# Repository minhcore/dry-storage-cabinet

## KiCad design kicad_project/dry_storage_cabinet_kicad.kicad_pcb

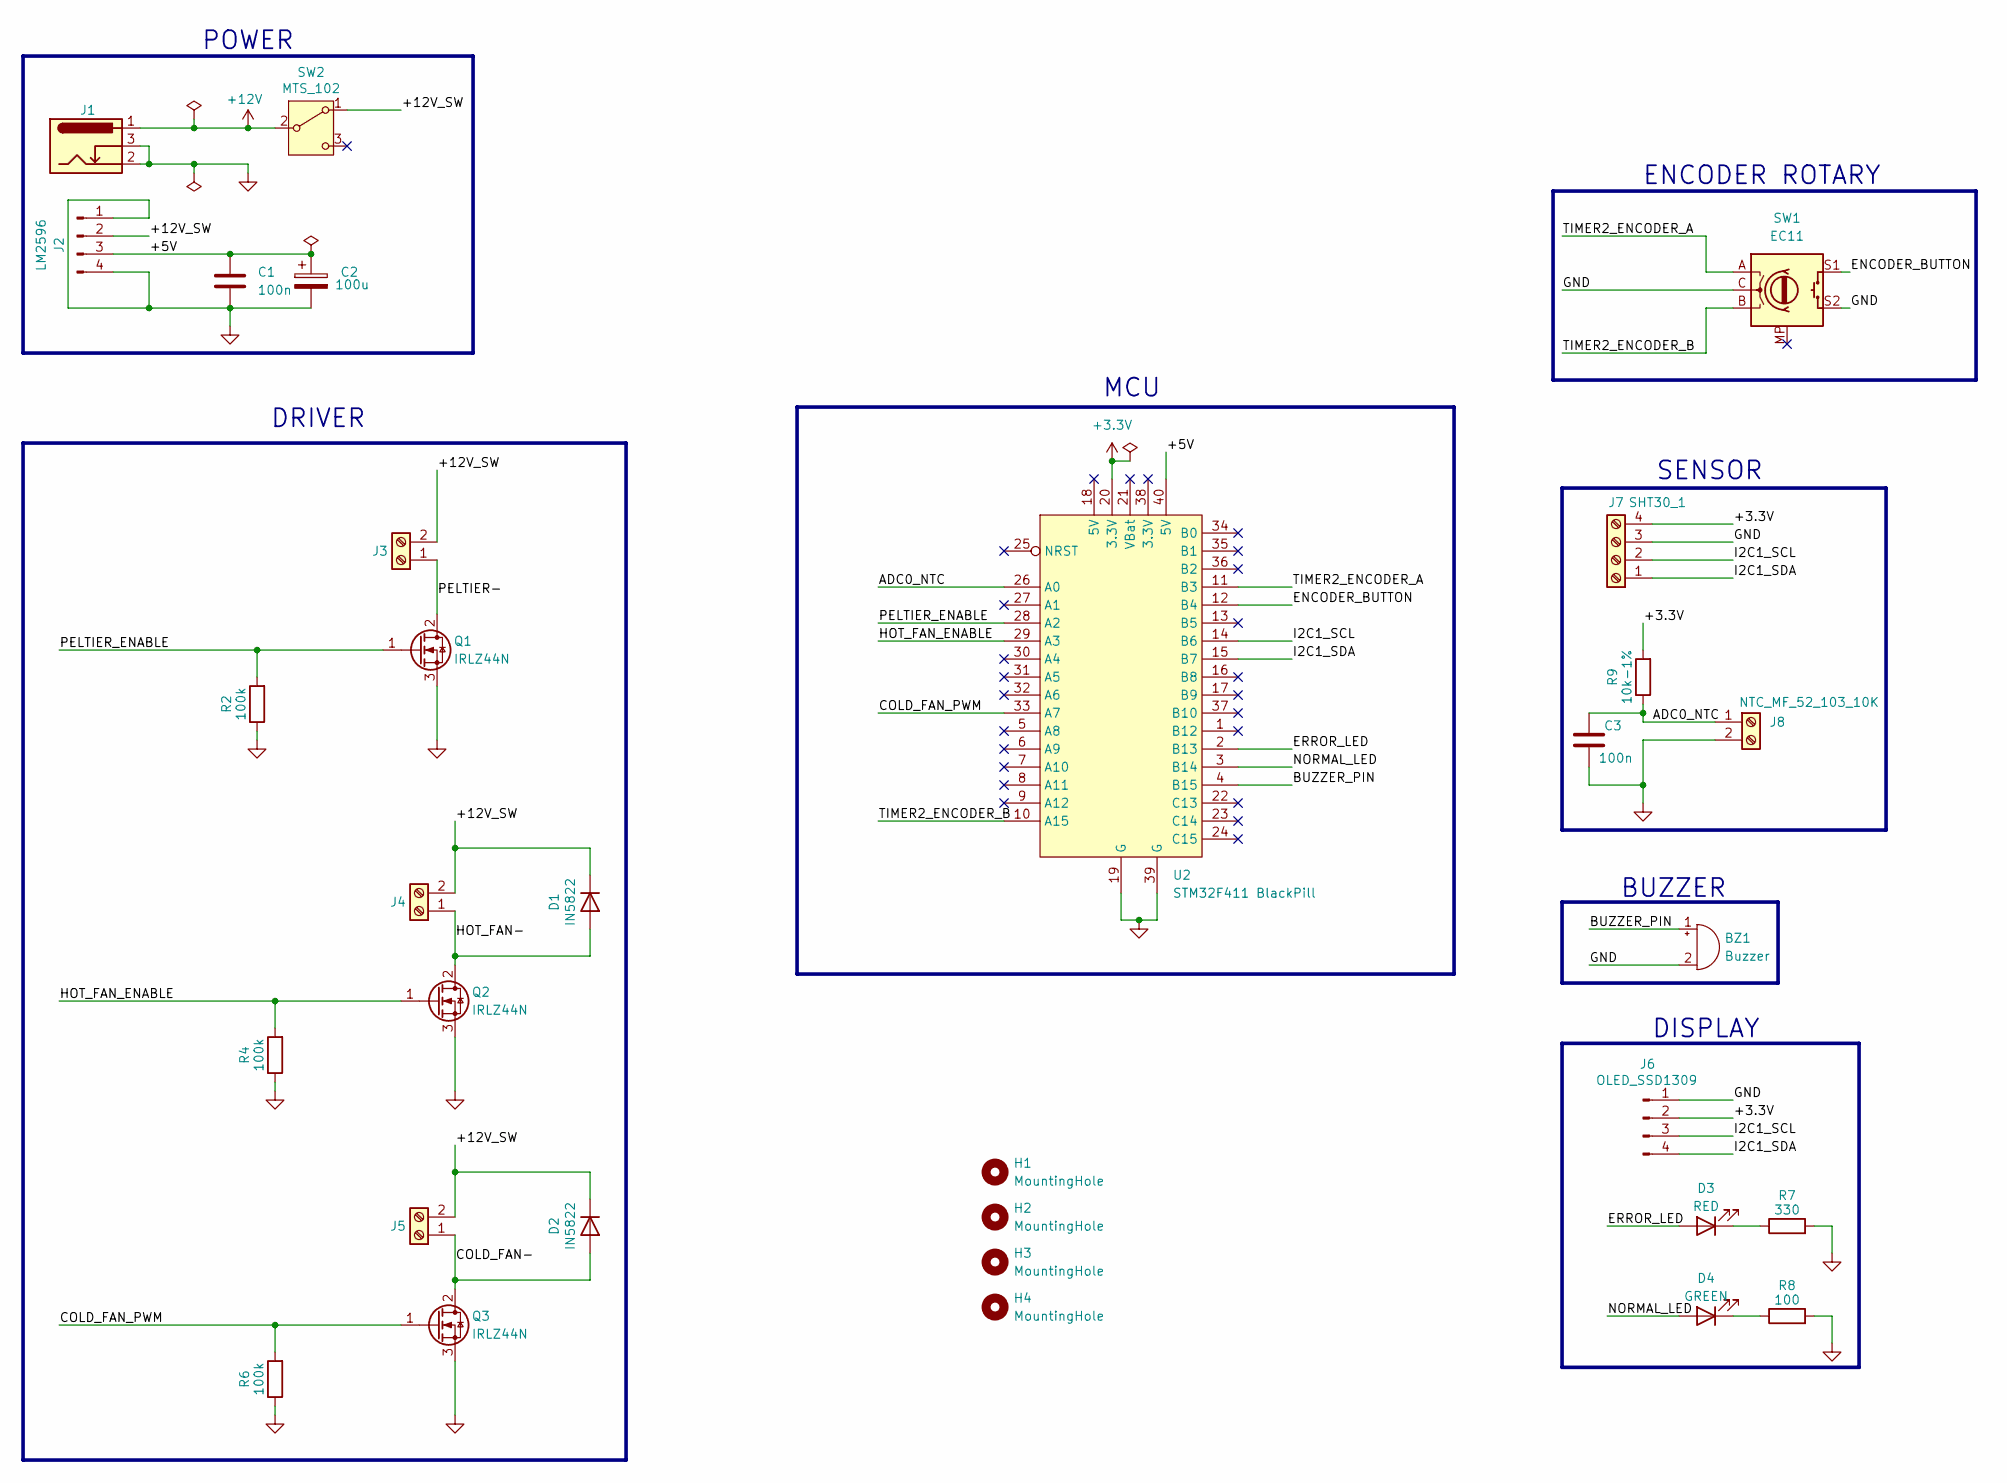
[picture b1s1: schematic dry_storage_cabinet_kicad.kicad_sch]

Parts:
BZ1: Buzzer; Buzzer_12x9.5RM7.6
C1, C3: 100n; C_Disc_D5.0mm_W2.5mm_P5.00mm
C2: 100u; CP_Radial_D6.3mm_P2.50mm
D1, D2: IN5822; D_DO-201AD_P15.24mm_Horizontal
D3: RED; LED_D3.0mm
D4: GREEN; LED_D3.0mm
H1, H2, H3, H4: MountingHole; MountingHole_3.2mm_M3
J1: Barrel_Jack_Switch; BarrelJack_GCT_DCJ200-10-A_Horizontal
J2: LM2596; LM2596-DC-DC
J3, J4, J5: Screw_Terminal_01x02; TerminalBlock_MaiXu_MX126-5.0-02P_1x02_P5.00mm
J6: OLED_SSD1309; PinHeader_1x04_P2.54mm_Vertical
J7: SHT30_1; TerminalBlock_MaiXu_MX126-5.0-04P_1x04_P5.00mm
J8: NTC_MF_52_103_10K; TerminalBlock_MaiXu_MX126-5.0-02P_1x02_P5.00mm
Q1, Q2, Q3: IRLZ44N; TO-220-3_Vertical
R2, R4, R6: 100k; R_Axial_DIN0207_L6.3mm_D2.5mm_P10.16mm_Horizontal
R7: 330; R_Axial_DIN0207_L6.3mm_D2.5mm_P10.16mm_Horizontal
R8: 100; R_Axial_DIN0207_L6.3mm_D2.5mm_P10.16mm_Horizontal
R9: 10k-1%; R_Axial_DIN0207_L6.3mm_D2.5mm_P10.16mm_Horizontal
SW1: EC11; RotaryEncoder_Alps_EC11E-Switch_Vertical_H20mm_MountingHoles
SW2: MTS_102; MTS102
U2: STM32F411 BlackPill; STM32F411_Black_Pill

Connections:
+3.3V: J6.2, J7.4, R9.2, U2.20 (3.3V)
+12V: J1.1, SW2.2 (B)
/+5V: C1.1, C2.1, J2.3, U2.40 (5V)
/+12V_SW: D1.1 (K), D2.1 (K), J2.2, J3.2, J4.2, J5.2, SW2.1 (A)
/ADC0_NTC: C3.1, J8.1, R9.1, U2.26 (A0)
/BUZZER_PIN: BZ1.1 (+), U2.4 (B15)
/COLD_FAN-: D2.2 (A), J5.1, Q3.2 (D)
/COLD_FAN_PWM: Q3.1 (G), R6.2, U2.33 (A7)
/ENCODER_BUTTON: SW1.S1, U2.12 (B4)
/ERROR_LED: D3.2 (A), U2.2 (B13)
/HOT_FAN-: D1.2 (A), J4.1, Q2.2 (D)
/HOT_FAN_ENABLE: Q2.1 (G), R4.2, U2.29 (A3)
/I2C1_SCL: J6.3, J7.2, U2.14 (B6)
/I2C1_SDA: J6.4, J7.1, U2.15 (B7)
/NORMAL_LED: D4.2 (A), U2.3 (B14)
/PELTIER-: J3.1, Q1.2 (D)
/PELTIER_ENABLE: Q1.1 (G), R2.2, U2.28 (A2)
/TIMER2_ENCODER_A: SW1.A, U2.11 (B3)
/TIMER2_ENCODER_B: SW1.B, U2.10 (A15)
GND: BZ1.2 (-), C1.2, C2.2, C3.2, J1.2, J1.3, J2.1, J2.4, J6.1, J7.3, J8.2, Q1.3 (S), Q2.3 (S), Q3.3 (S), R2.1, R4.1, R6.1, R7.2, R8.2, SW1.C, SW1.S2, U2.19 (G), U2.39 (G)
unnamed: D3.1 (K), R7.1
unnamed: D4.1 (K), R8.1

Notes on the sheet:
BUZZER
DRIVER
ENCODER ROTARY
POWER
DISPLAY
MCU
SENSOR

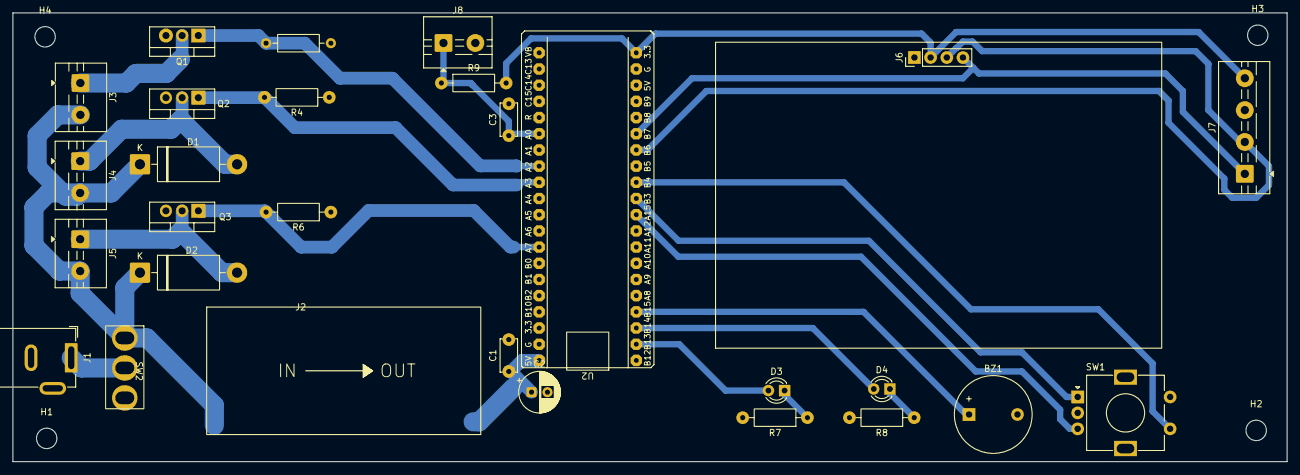
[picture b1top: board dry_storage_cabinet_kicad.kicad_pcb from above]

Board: 2 copper layers, 199.9 x 70.4 mm, 32 parts (0 on the bottom side), 22 nets.

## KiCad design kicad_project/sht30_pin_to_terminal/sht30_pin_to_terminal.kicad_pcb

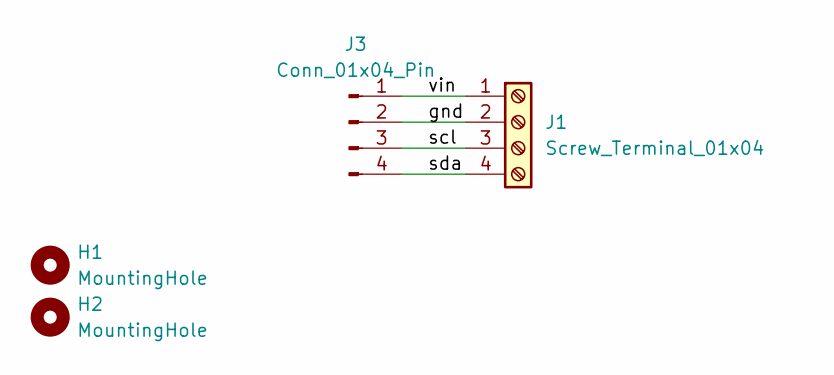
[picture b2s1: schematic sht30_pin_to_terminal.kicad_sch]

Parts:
H1, H2: MountingHole; MountingHole_3.2mm_M3
J1: Screw_Terminal_01x04; TerminalBlock_MaiXu_MX126-5.0-04P_1x04_P5.00mm
J3: Conn_01x04_Pin; PinHeader_1x04_P2.54mm_Vertical

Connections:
/gnd: J1.2, J3.2
/scl: J1.3, J3.3
/sda: J1.4, J3.4
/vin: J1.1, J3.1

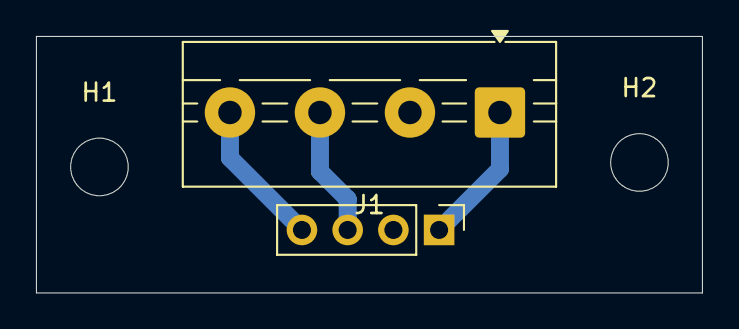
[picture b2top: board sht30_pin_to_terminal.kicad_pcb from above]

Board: 2 copper layers, 37.0 x 14.2 mm, 4 parts (0 on the bottom side), 4 nets.

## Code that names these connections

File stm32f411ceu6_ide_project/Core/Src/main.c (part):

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/* Private define ------------------------------------------------------------*/
/* USER CODE BEGIN PD */
#define STATUS_PORT 				GPIOB
#define ERROR_LED_PIN 				GPIO_PIN_13
#define PELTIER_LED_PIN 			GPIO_PIN_14
#define BUZZER_PIN 					GPIO_PIN_15

#define DRIVER_PORT					GPIOA
#define PELTIER_PIN 				GPIO_PIN_2
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#define COLD_FAN_TIM_HANDLE			&htim3
#define COLD_FAN_CHANNEL 			TIM_CHANNEL_2

#define ENCODER_BUTTON_PIN			GPIO_PIN_4
#define ENCODER_MAIN_TIM_HANDLE		&htim2
#define ENCODER_TICK_TIM_HANDLE		&htim4

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	// stop all the loads except Hot Fan, leave it to cool down Peltier
	HAL_GPIO_WritePin(DRIVER_PORT, PELTIER_PIN, 0);
	HAL_TIM_PWM_Stop(COLD_FAN_TIM_HANDLE, COLD_FAN_CHANNEL);
	HAL_GPIO_WritePin(STATUS_PORT, BUZZER_PIN, 0);
	HAL_GPIO_WritePin(STATUS_PORT, PELTIER_LED_PIN, 0);
	HAL_GPIO_WritePin(DRIVER_PORT, HOT_FAN_PIN, 1);
}
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
	if ((HAL_GetTick() - error_tick) >= 500)
	{
		HAL_GPIO_TogglePin(STATUS_PORT, ERROR_LED_PIN);
		error_tick = HAL_GetTick();
	}

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  //

  // ENCODER EC11
  encoder_init(&encoder, ENCODER_MAIN_TIM_HANDLE, ENCODER_BUTTON_PIN);
  HAL_TIM_Base_Start_IT(ENCODER_TICK_TIM_HANDLE);
  //

  // POWER DRIVER
  control_init(&control, COLD_FAN_TIM_HANDLE, COLD_FAN_CHANNEL,
		  DRIVER_PORT, PELTIER_PIN, DRIVER_PORT, HOT_FAN_PIN,
		  STATUS_PORT, PELTIER_LED_PIN, STATUS_PORT, BUZZER_PIN);
  //

  // FSM INIT
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
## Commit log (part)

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2026-06-23 create basic folder for kicad
2026-06-24 Testing oled driver & encoder driver
2026-06-25 design menu interface, process about 25%
2026-06-30 Get ready to testing i2c 20 cm cable
2026-06-30 Get ready for real test on the cabinet

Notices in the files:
stm32f411ceu6_ide_project/Core/Src/main.c:
Copyright (c) 2026 STMicroelectronics.
All rights reserved.
This software is licensed under terms that can be found in the LICENSE file
